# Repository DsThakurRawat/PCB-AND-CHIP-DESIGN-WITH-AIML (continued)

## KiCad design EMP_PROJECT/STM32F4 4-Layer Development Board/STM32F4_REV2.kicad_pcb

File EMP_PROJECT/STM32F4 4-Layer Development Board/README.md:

# STM32F4 4-Layer Development Board

**Project**: STM32F405RGT6 4-Layer Reference Development Board  
**Course / Subject**: Electronics Manufacturing & PCB Design (EMP)  
**Submission Date**: November 8, 2026  

---

## 👥 Team Details
* **Divyansh Rawat** (Lead Hardware & Validation Engineer) — **Roll No: 124EC0030**
* Rehan Afroz — **Roll No: 124EC0033**
* Ishan Pandey — **Roll No: 124EC0032**
* Dasari E S T Vishnu Vardhan — **Roll No: 124EC0010**

---

## 📜 Attribution & Provenance
This hardware design is adapted and re-routed from the open-source **STM32F4 Reference Design** by **Philip Salmony (Phil's Lab)**.  
In compliance with the **MIT License**, the original copyright and license terms are preserved in full in the accompanying [`LICENSE`](file:///home/divyansh-rawat/AIPCBDESIGN/EMP_PROJECT/STM32F4%204-Layer%20Development%20Board/LICENSE) file. The layout has been adapted for KiCad 9, with custom design rules, optimized copper plane definitions, and re-generated turnkey manufacturing deliverables.

---

## 🚀 Key Specifications
* **Microcontroller**: STMicroelectronics STM32F405RGT6 (Arm Cortex-M4, 168 MHz, 1MB Flash, 192KB SRAM, LQFP-64)
* **Stackup**: 4 Layers (F.Cu Signal - In1.Cu Solid GND - In2.Cu Solid +3.3V - B.Cu Signal/GND)
* **Power Supply**: Dual-input (7V–24V DC Screw Terminal & 5V USB-C) stepping down to +3.3V via MPS MP2359 1.4 MHz buck converter
* **USB Interface**: USB 2.0 Full-Speed Type-C with ST USBLC6-2SC6 low-capacitance ESD protection
* **Oscillator**: 16.000 MHz fundamental-mode crystal conforming to ST AN2867 gain margin standards
* **Debug**: Standardized 4-pin SWD programming header

---

## 📁 Package Manifest
- [`STM32F4_REV2.kicad_sch`](file:///home/divyansh-rawat/AIPCBDESIGN/EMP_PROJECT/STM32F4%204-Layer%20Development%20Board/STM32F4_REV2.kicad_sch) — Native KiCad 9 Schematic (0 ERC violations)
- [`STM32F4_REV2.kicad_pcb`](file:///home/divyansh-rawat/AIPCBDESIGN/EMP_PROJECT/STM32F4%204-Layer%20Development%20Board/STM32F4_REV2.kicad_pcb) — Native KiCad 9 Layout (0 DRC violations, 0 unconnected items)
- [`STM32F4_REV2.kicad_pro`](file:///home/divyansh-rawat/AIPCBDESIGN/EMP_PROJECT/STM32F4%204-Layer%20Development%20Board/STM32F4_REV2.kicad_pro) — KiCad 9 Project settings & design rules
- [`STM32F4_REV2.kicad_sym`](file:///home/divyansh-rawat/AIPCBDESIGN/EMP_PROJECT/STM32F4%204-Layer%20Development%20Board/STM32F4_REV2.kicad_sym) — Project symbol library cache
- [`manufacturing/`](file:///home/divyansh-rawat/AIPCBDESIGN/EMP_PROJECT/STM32F4%204-Layer%20Development%20Board/manufacturing/)
  - `STM32F4_REV2_gerbers.zip` — Production-ready Gerber & Excellon drill archive
  - `STM32F4_REV2_bom.csv` — Reconciled manufacturing Bill of Materials
  - `STM32F4_REV2_pos.csv` — Pick-and-place centroid positions
  - `STM32F4_REV2_schematic.pdf` & `STM32F4_REV2.pdf` — Vector schematic and layout plots
  - `ibom.html` — Interactive visual assembly BOM
  - `STM32F4_REV2_3d.png` — 3D raytraced rendering of current board
- [`DESIGN_CONSIDERATIONS.md`](file:///home/divyansh-rawat/AIPCBDESIGN/EMP_PROJECT/STM32F4%204-Layer%20Development%20Board/DESIGN_CONSIDERATIONS.md) — Comprehensive engineering caveats, calculations, and bring-up checklist
- [`PRESENTATION.md`](file:///home/divyansh-rawat/AIPCBDESIGN/EMP_PROJECT/STM32F4%204-Layer%20Development%20Board/PRESENTATION.md) — Slide deck presentation and review document
- [`verification/`](file:///home/divyansh-rawat/AIPCBDESIGN/EMP_PROJECT/STM32F4%204-Layer%20Development%20Board/verification/)
  - `erc-rerun.json` & `erc-rerun.rpt` (0 errors, 0 warnings)
  - `drc-rerun.json` & `drc-rerun.rpt` (0 violations, 0 unconnected, 0 parity issues)
  - `gerbers-check/` (freshly plotted verification Gerbers)

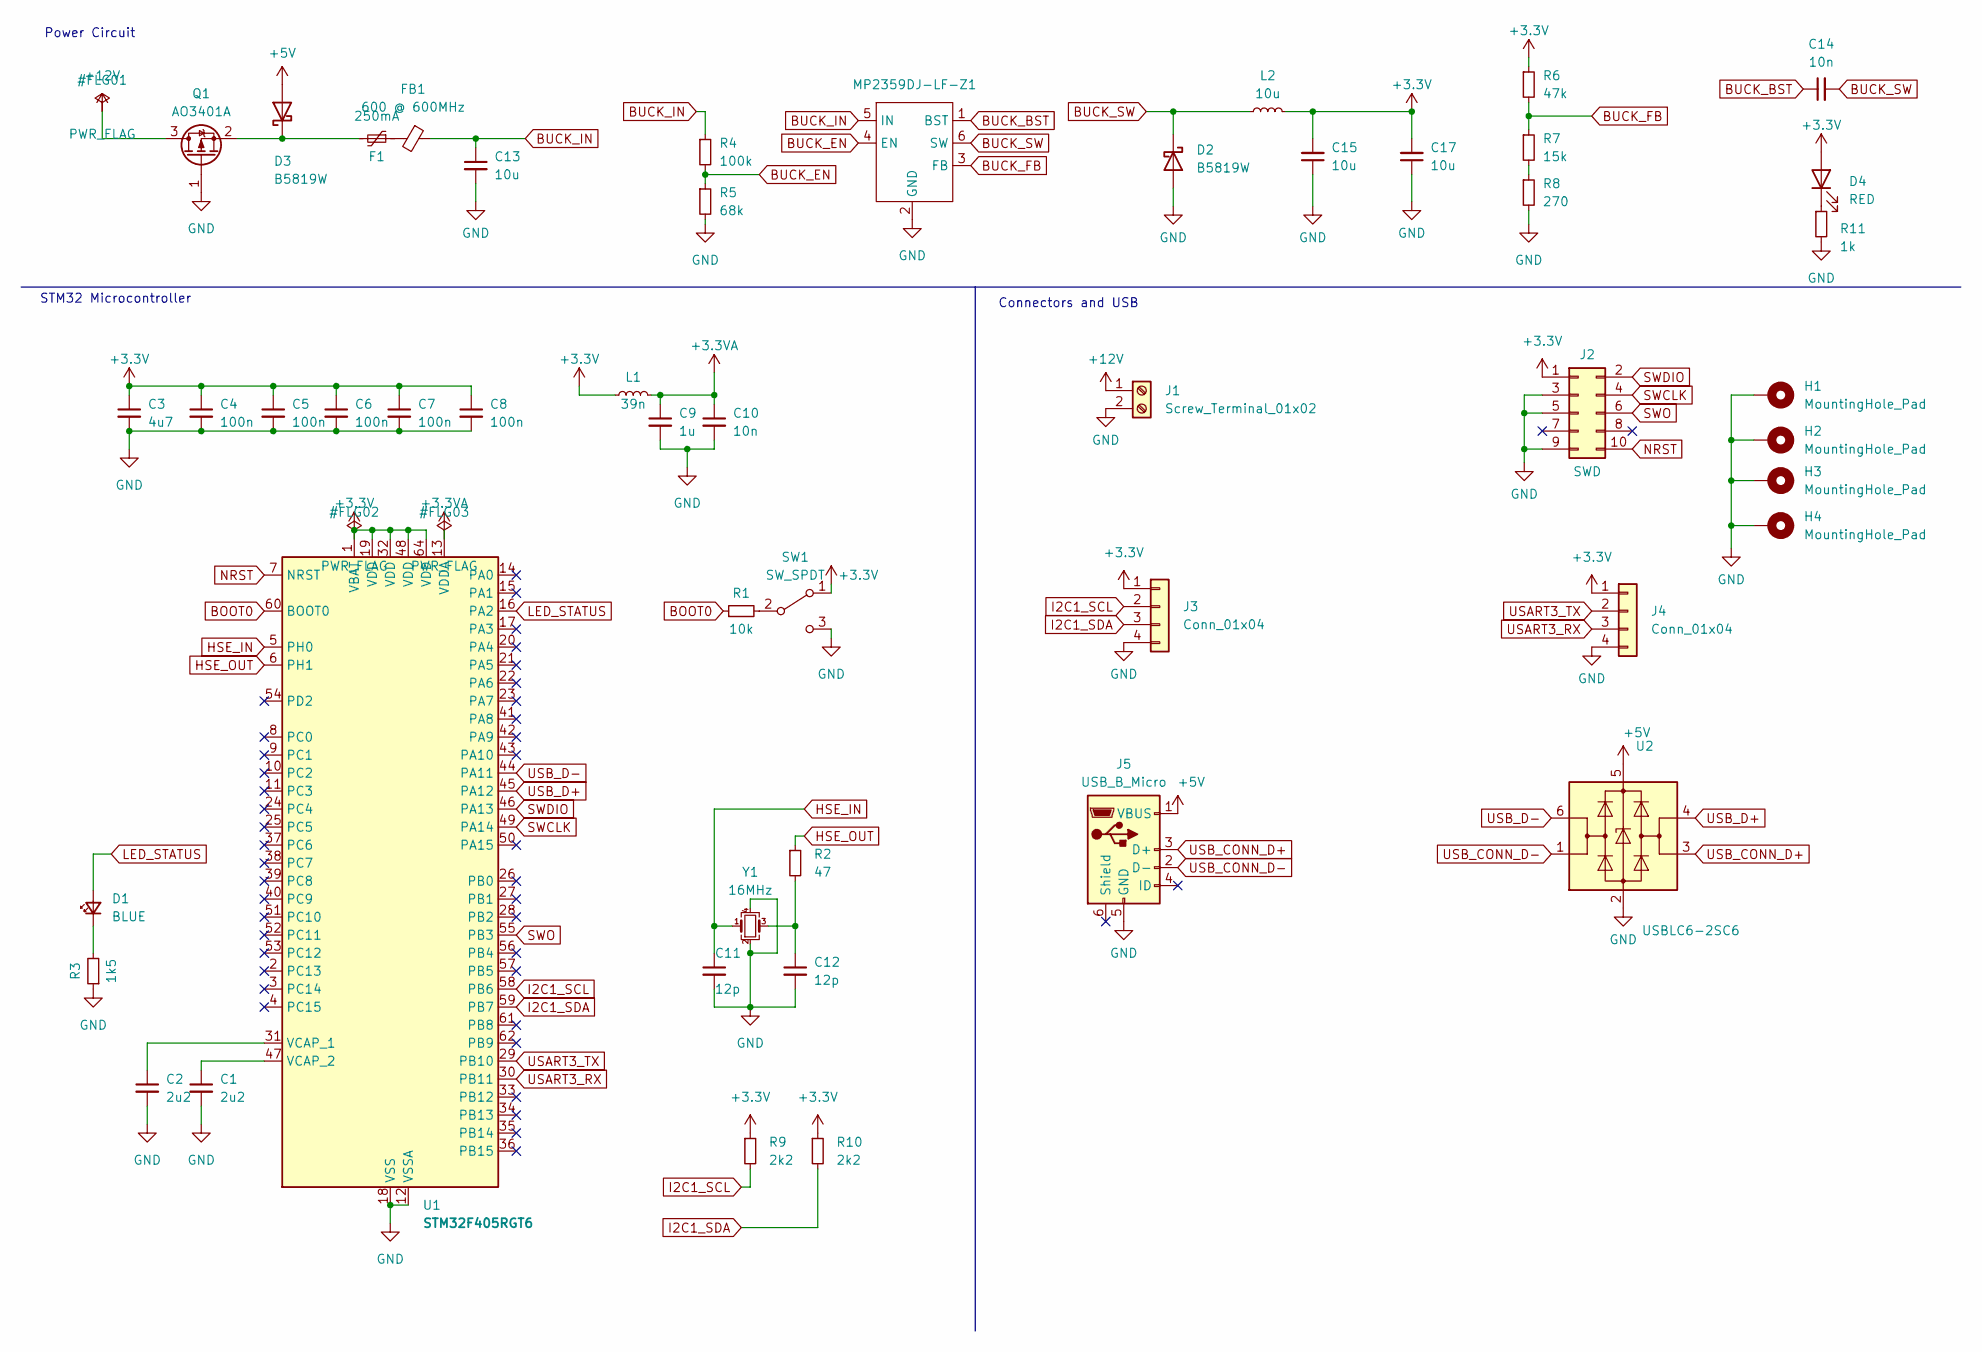
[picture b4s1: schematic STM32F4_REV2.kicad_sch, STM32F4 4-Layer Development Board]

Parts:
C1, C2: 2u2; C_0603_1608Metric
C3: 4u7; C_0603_1608Metric
C4, C5, C6, C7, C8: 100n; C_0402_1005Metric
C9: 1u; C_0402_1005Metric
C10: 10n; C_0402_1005Metric
C11, C12: 12p; C_0402_1005Metric
C13, C15, C17: 10u; C_1206_3216Metric
C14: 10n; C_0603_1608Metric
D1: BLUE; LED_0603_1608Metric
D2, D3: B5819W; D_SOD-123
D4: RED; LED_0603_1608Metric
F1: 250mA; Fuse_1206_3216Metric
FB1: 600 @ 600MHz; L_0805_2012Metric
H1, H2, H3, H4: MountingHole_Pad; MountingHole_4.3mm_M4_Pad_Via
J1: Screw_Terminal_01x02; TerminalBlock_Phoenix_PT-1,5-2-3.5-H_1x02_P3.50mm_Horizontal
J2: SWD; PinHeader_2x05_P1.27mm_Vertical_SMD
J3, J4: Conn_01x04; Molex_PicoBlade_53048-0410_1x04_P1.25mm_Horizontal
J5: USB_B_Micro; USB_Micro-B_GCT_USB3076-30-A
L1: 39n; L_0402_1005Metric
L2: 10u; L_TracoPower_TCK-047_5.2x5.8mm
MP2359DJ-LF-Z1: SOT-23-6
Q1: AO3401A; SOT-23
R1: 10k; R_0402_1005Metric
R2: 47; R_0402_1005Metric
R3: 1k5; R_0603_1608Metric
R4: 100k; R_0603_1608Metric
R5: 68k; R_0603_1608Metric
R6: 47k; R_0603_1608Metric
R7: 15k; R_0603_1608Metric
R8: 270; R_0603_1608Metric
R9, R10: 2k2; R_0402_1005Metric
R11: 1k; R_0603_1608Metric
SW1: SW_SPDT; SW_SPDT_PCM12
U1: STM32F405RGT6; LQFP-64_10x10mm_P0.5mm
U2: USBLC6-2SC6; SOT-23-6
Y1: 16MHz; Crystal_SMD_3225-4Pin_3.2x2.5mm

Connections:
+3.3V: C3.1, C4.1, C5.1, C6.1, C7.1, C8.1, C15.2, C17.2, D4.2 (A), J2.1, J3.1, J4.1, L1.1, L2.2, R6.1, R9.1, R10.1, SW1.1 (A), U1.1 (VBAT), U1.19 (VDD), U1.32 (VDD), U1.48 (VDD), U1.64 (VDD)
+3.3VA: C9.1, C10.1, L1.2, U1.13 (VDDA)
+5V: D3.2 (A), J5.1 (VBUS), U2.5 (VBUS)
+12V: J1.1, Q1.3 (D)
BOOT0: R1.1, U1.60 (BOOT0)
BUCK_BST: C14.1, MP2359DJ-LF-Z1.1 (BST)
BUCK_EN: MP2359DJ-LF-Z1.4 (EN), R4.2, R5.1
BUCK_FB: MP2359DJ-LF-Z1.3 (FB), R6.2, R7.1
BUCK_IN: C13.1, FB1.1, MP2359DJ-LF-Z1.5 (IN), R4.1
BUCK_SW: C14.2, D2.1 (K), L2.1, MP2359DJ-LF-Z1.6 (SW)
GND: C1.2, C2.2, C3.2, C4.2, C5.2, C6.2, C7.2, C8.2, C9.2, C10.2, C11.2, C12.2, C13.2, C15.1, C17.1, D2.2 (A), H1.1, H2.1, H3.1, H4.1, J1.2, J2.3, J2.5, J2.9, J3.4, J4.4, J5.5 (GND), MP2359DJ-LF-Z1.2 (GND), Q1.1 (G), R3.1, R5.2, R8.2, R11.2, SW1.3 (C), U1.12 (VSSA), U1.18 (VSS), U1.63 (VSS), U2.2 (GND), Y1.2, Y1.4
HSE_IN: C11.1, U1.5 (PH0), Y1.1
HSE_OUT: R2.1, U1.6 (PH1)
I2C1_SCL: J3.2, R9.2, U1.58 (PB6)
I2C1_SDA: J3.3, R10.2, U1.59 (PB7)
LED_STATUS: D1.2 (A), U1.16 (PA2)
NRST: J2.10, U1.7 (NRST)
unnamed: C12.1, R2.2, Y1.3
unnamed: D1.1 (K), R3.2
unnamed: D3.1 (K), F1.2, Q1.2 (S)
unnamed: D4.1 (K), R11.1
unnamed: F1.1, FB1.2
unnamed: R7.2, R8.1
unnamed: R1.2, SW1.2 (B)
unnamed: C2.1, U1.31 (VCAP_1)
unnamed: C1.1, U1.47 (VCAP_2)
SWCLK: J2.4, U1.49 (PA14)
SWDIO: J2.2, U1.46 (PA13)
SWO: J2.6, U1.55 (PB3)
USART3_RX: J4.3, U1.30 (PB11)
USART3_TX: J4.2, U1.29 (PB10)
USB_CONN_D+: J5.3 (D+), U2.3 (I/O2)
USB_CONN_D-: J5.2 (D-), U2.1 (I/O1)
USB_D+: U1.45 (PA12), U2.4 (I/O2)
USB_D-: U1.44 (PA11), U2.6 (I/O1)

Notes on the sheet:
Power Circuit
STM32 Microcontroller
Connectors and USB

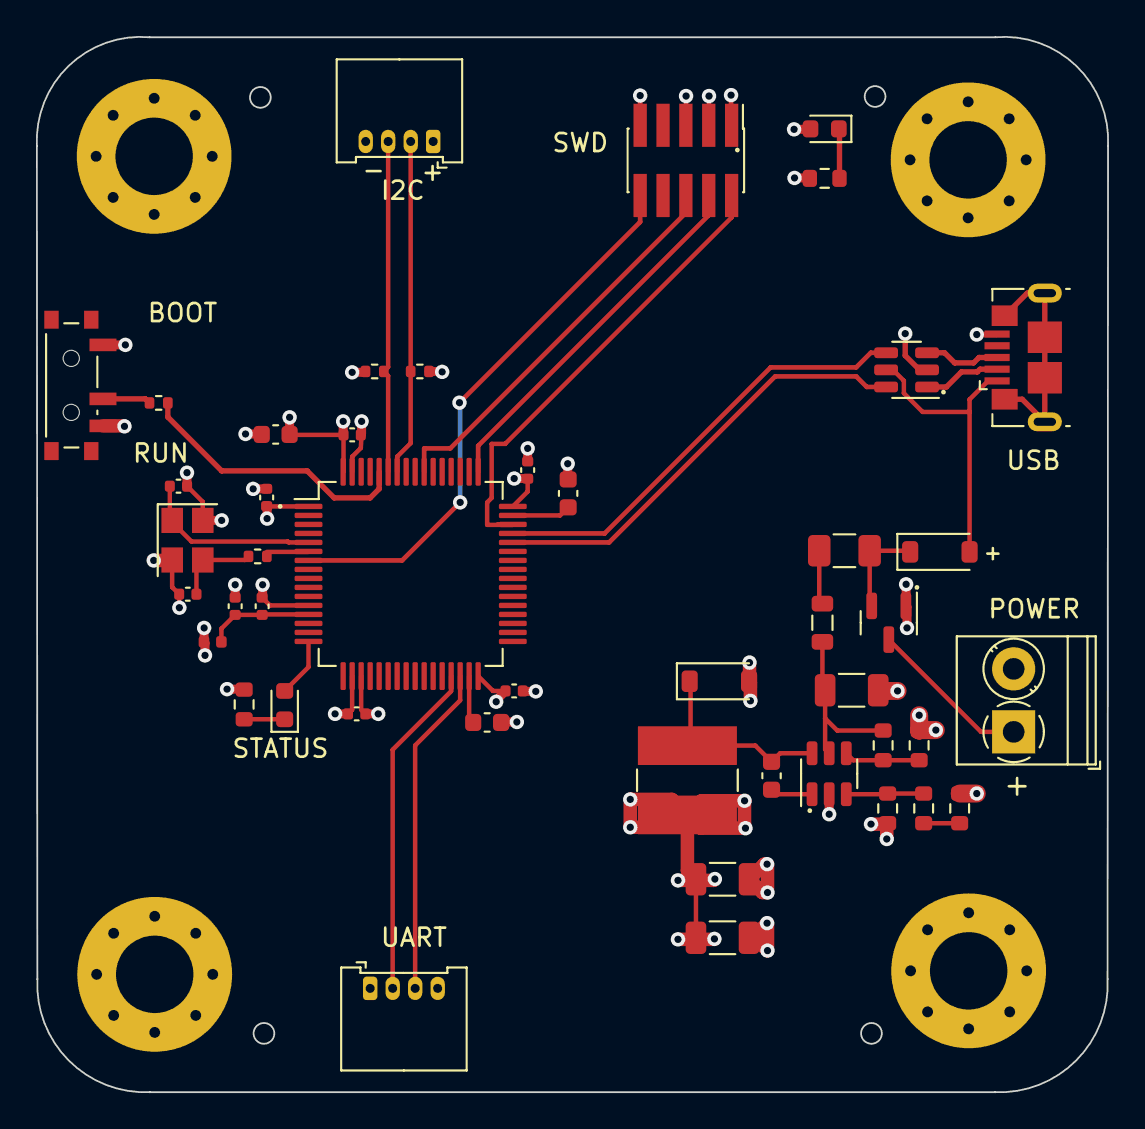
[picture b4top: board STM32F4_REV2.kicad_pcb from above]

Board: 4 copper layers, 59.5 x 58.6 mm, 50 parts (0 on the bottom side), 35 nets.

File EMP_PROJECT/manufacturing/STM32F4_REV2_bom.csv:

"Refs","Value","Footprint","Qty","DNP"
"C1","2u2","Capacitor_SMD:C_0603_1608Metric","1",""
"C2","2u2","Capacitor_SMD:C_0603_1608Metric","1",""
"C3","4u7","Capacitor_SMD:C_0603_1608Metric","1",""
"C4","100n","Capacitor_SMD:C_0402_1005Metric","1",""
"C5","100n","Capacitor_SMD:C_0402_1005Metric","1",""
"C6","100n","Capacitor_SMD:C_0402_1005Metric","1",""
"C7","100n","Capacitor_SMD:C_0402_1005Metric","1",""
"C8","100n","Capacitor_SMD:C_0402_1005Metric","1",""
"C9","1u","Capacitor_SMD:C_0402_1005Metric","1",""
"C10","10n","Capacitor_SMD:C_0402_1005Metric","1",""
"C11","12p","Capacitor_SMD:C_0402_1005Metric","1",""
"C12","12p","Capacitor_SMD:C_0402_1005Metric","1",""
"C13","10u","Capacitor_SMD:C_1206_3216Metric","1",""
"C14","10n","Capacitor_SMD:C_0603_1608Metric","1",""
"C15","10u","Capacitor_SMD:C_1206_3216Metric","1",""
"C17","10u","Capacitor_SMD:C_1206_3216Metric","1",""
"D1","BLUE","LED_SMD:LED_0603_1608Metric","1",""
"D2","B5819W","Diode_SMD:D_SOD-123","1",""
"D3","B5819W","Diode_SMD:D_SOD-123","1",""
"D4","RED","LED_SMD:LED_0603_1608Metric","1",""
"F1","250mA","Fuse:Fuse_1206_3216Metric","1",""
"FB1","600 @ 600MHz","Inductor_SMD:L_0805_2012Metric","1",""
"H1","MountingHole_Pad","MountingHole:MountingHole_4.3mm_M4_Pad_Via","1",""
"H2","MountingHole_Pad","MountingHole:MountingHole_4.3mm_M4_Pad_Via","1",""
"H3","MountingHole_Pad","MountingHole:MountingHole_4.3mm_M4_Pad_Via","1",""
"H4","MountingHole_Pad","MountingHole:MountingHole_4.3mm_M4_Pad_Via","1",""
"J1","Screw_Terminal_01x02","TerminalBlock_Phoenix:TerminalBlock_Phoenix_PT-1,5-2-3.5-H_1x02_P3.50mm_Horizontal","1",""
"J2","SWD","Connector_PinHeader_1.27mm:PinHeader_2x05_P1.27mm_Vertical_SMD","1",""
"J3","Conn_01x04","Connector_Molex:Molex_PicoBlade_53048-0410_1x04_P1.25mm_Horizontal","1",""
"J4","Conn_01x04","Connector_Molex:Molex_PicoBlade_53048-0410_1x04_P1.25mm_Horizontal","1",""
"J5","USB_B_Micro","Connector_USB:USB_Micro-B_GCT_USB3076-30-A","1",""
"L1","39n","Inductor_SMD:L_0402_1005Metric","1",""
"L2","10u","Inductor_SMD:L_TracoPower_TCK-047_5.2x5.8mm","1",""
"MP2359DJ-LF-Z1","~","Package_TO_SOT_SMD:SOT-23-6","1",""
"Q1","AO3401A","Package_TO_SOT_SMD:SOT-23","1",""
"R1","10k","Resistor_SMD:R_0402_1005Metric","1",""
"R2","47","Resistor_SMD:R_0402_1005Metric","1",""
"R3","1k5","Resistor_SMD:R_0603_1608Metric","1",""
"R4","100k","Resistor_SMD:R_0603_1608Metric","1",""
"R5","68k","Resistor_SMD:R_0603_1608Metric","1",""
"R6","47k","Resistor_SMD:R_0603_1608Metric","1",""
"R7","15k","Resistor_SMD:R_0603_1608Metric","1",""
"R8","270","Resistor_SMD:R_0603_1608Metric","1",""
"R9","2k2","Resistor_SMD:R_0402_1005Metric","1",""
"R10","2k2","Resistor_SMD:R_0402_1005Metric","1",""
"R11","1k","Resistor_SMD:R_0603_1608Metric","1",""
"SW1","SW_SPDT","Button_Switch_SMD:SW_SPDT_PCM12","1",""
"U1","STM32F405RGT6","Package_QFP:LQFP-64_10x10mm_P0.5mm","1",""
"U2","USBLC6-2SC6","Package_TO_SOT_SMD:SOT-23-6","1",""
"Y1","16MHz","Crystal:Crystal_SMD_3225-4Pin_3.2x2.5mm","1",""

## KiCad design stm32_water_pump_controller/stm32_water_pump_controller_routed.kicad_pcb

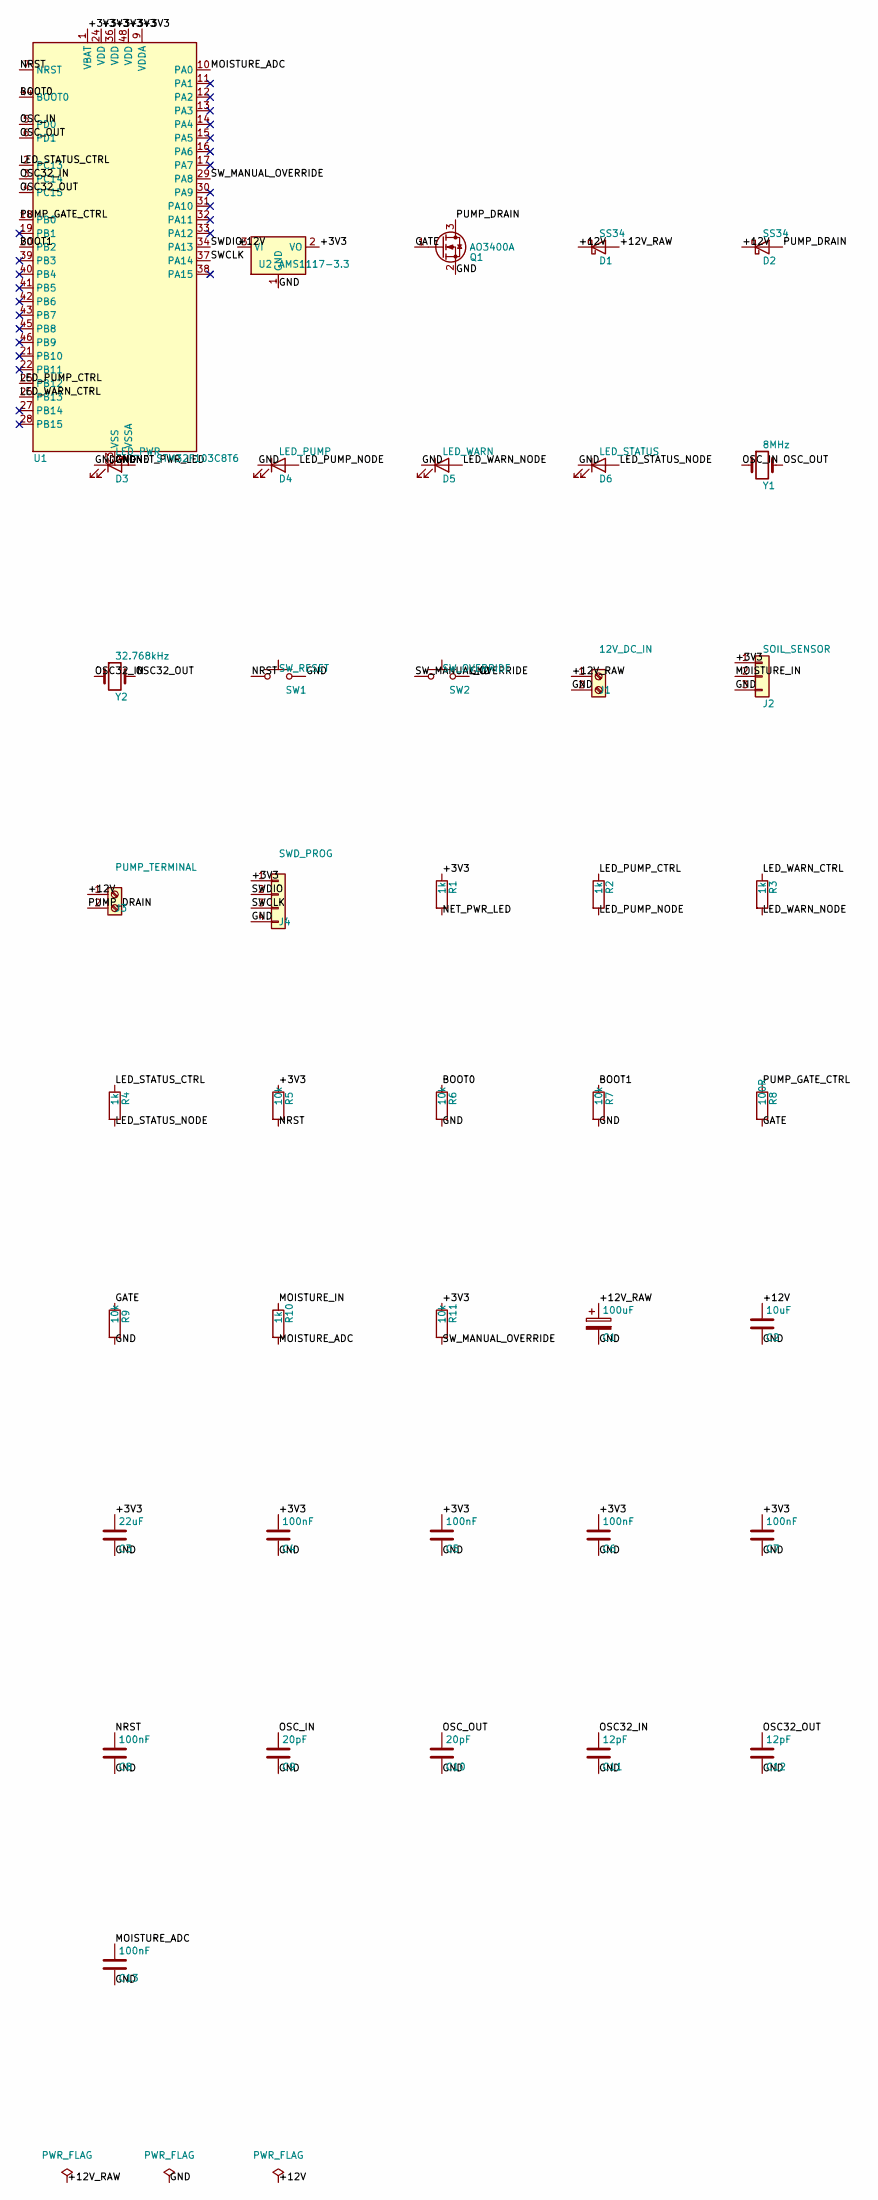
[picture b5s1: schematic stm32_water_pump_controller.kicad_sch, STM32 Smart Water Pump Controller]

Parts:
C1: 100uF; CP_Radial_D6.3mm_P2.50mm
C2: 10uF; C_0805_2012Metric
C3: 22uF; C_0805_2012Metric
C4, C5, C6, C7, C8, C13: 100nF; C_0805_2012Metric
C9, C10: 20pF; C_0805_2012Metric
C11, C12: 12pF; C_0805_2012Metric
D1, D2: SS34; D_SMA
D3: LED_PWR; LED_0805_2012Metric
D4: LED_PUMP; LED_0805_2012Metric
D5: LED_WARN; LED_0805_2012Metric
D6: LED_STATUS; LED_0805_2012Metric
J1: 12V_DC_IN; TerminalBlock_Phoenix_MKDS-1,5-2-5.08_1x02_P5.08mm_Horizont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
J2: SOIL_SENSOR; PinHeader_1x03_P2.54mm_Vertical
J3: PUMP_TERMINAL; TerminalBlock_Phoenix_MKDS-1,5-2-5.08_1x02_P5.08mm_Horizont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
J4: SWD_PROG; PinHeader_1x04_P2.54mm_Vertical
Q1: AO3400A; SOT-23
R1, R2, R3, R4, R10: 1k; R_0805_2012Metric
R5, R6, R7, R9, R11: 10k; R_0805_2012Metric
R8: 100R; R_0805_2012Metric
SW1: SW_RESET; SW_PUSH_6mm
SW2: SW_OVERRIDE; SW_PUSH_6mm
U1: STM32F103C8T6; LQFP-48_7x7mm_P0.5mm
U2: AMS1117-3.3; SOT-223-3_TabPin2
Y1: 8MHz; Crystal_SMD_5032-2Pin_5.0x3.2mm
Y2: 32.768kHz; Crystal_SMD_3215-2Pin_3.2x1.5mm

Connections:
+3V3: C3.1, C4.1, C5.1, C6.1, C7.1, J2.1, J4.1, R1.1, R5.1, R11.1, U1.1 (VBAT), U1.9 (VDDA), U1.24 (VDD), U1.36 (VDD), U1.48 (VDD), U2.2 (VO)
+12V: C2.1, D1.1 (K), D2.1 (K), J3.1, U2.3 (VI)
+12V_RAW: C1.1, D1.2 (A), J1.1
BOOT0: R6.1, U1.44 (BOOT0)
BOOT1: R7.1, U1.20 (PB2)
GATE: Q1.1 (G), R8.2, R9.1
GND: C1.2, C2.2, C3.2, C4.2, C5.2, C6.2, C7.2, C8.2, C9.2, C10.2, C11.2, C12.2, C13.2, D3.1 (K), D4.1 (K), D5.1 (K), D6.1 (K), J1.2, J2.3, J4.4, Q1.2 (S), R6.2, R7.2, R9.2, SW1.2, SW2.2, U1.8 (VSSA), U1.23 (VSS), U1.35 (VSS), U1.47 (VSS), U2.1 (GND)
LED_PUMP_CTRL: R2.1, U1.25 (PB12)
LED_PUMP_NODE: D4.2 (A), R2.2
LED_STATUS_CTRL: R4.1, U1.2 (PC13)
LED_STATUS_NODE: D6.2 (A), R4.2
LED_WARN_CTRL: R3.1, U1.26 (PB13)
LED_WARN_NODE: D5.2 (A), R3.2
MOISTURE_ADC: C13.1, R10.2, U1.10 (PA0)
MOISTURE_IN: J2.2, R10.1
NET_PWR_LED: D3.2 (A), R1.2
NRST: C8.1, R5.2, SW1.1, U1.7 (NRST)
OSC32_IN: C11.1, U1.3 (PC14), Y2.1
OSC32_OUT: C12.1, U1.4 (PC15), Y2.2
OSC_IN: C9.1, U1.5 (PD0), Y1.1
OSC_OUT: C10.1, U1.6 (PD1), Y1.2
PUMP_DRAIN: D2.2 (A), J3.2, Q1.3 (D)
PUMP_GATE_CTRL: R8.1, U1.18 (PB0)
SWCLK: J4.3, U1.37 (PA14)
SWDIO: J4.2, U1.34 (PA13)
SW_MANUAL_OVERRIDE: R11.2, SW2.1, U1.29 (PA8)

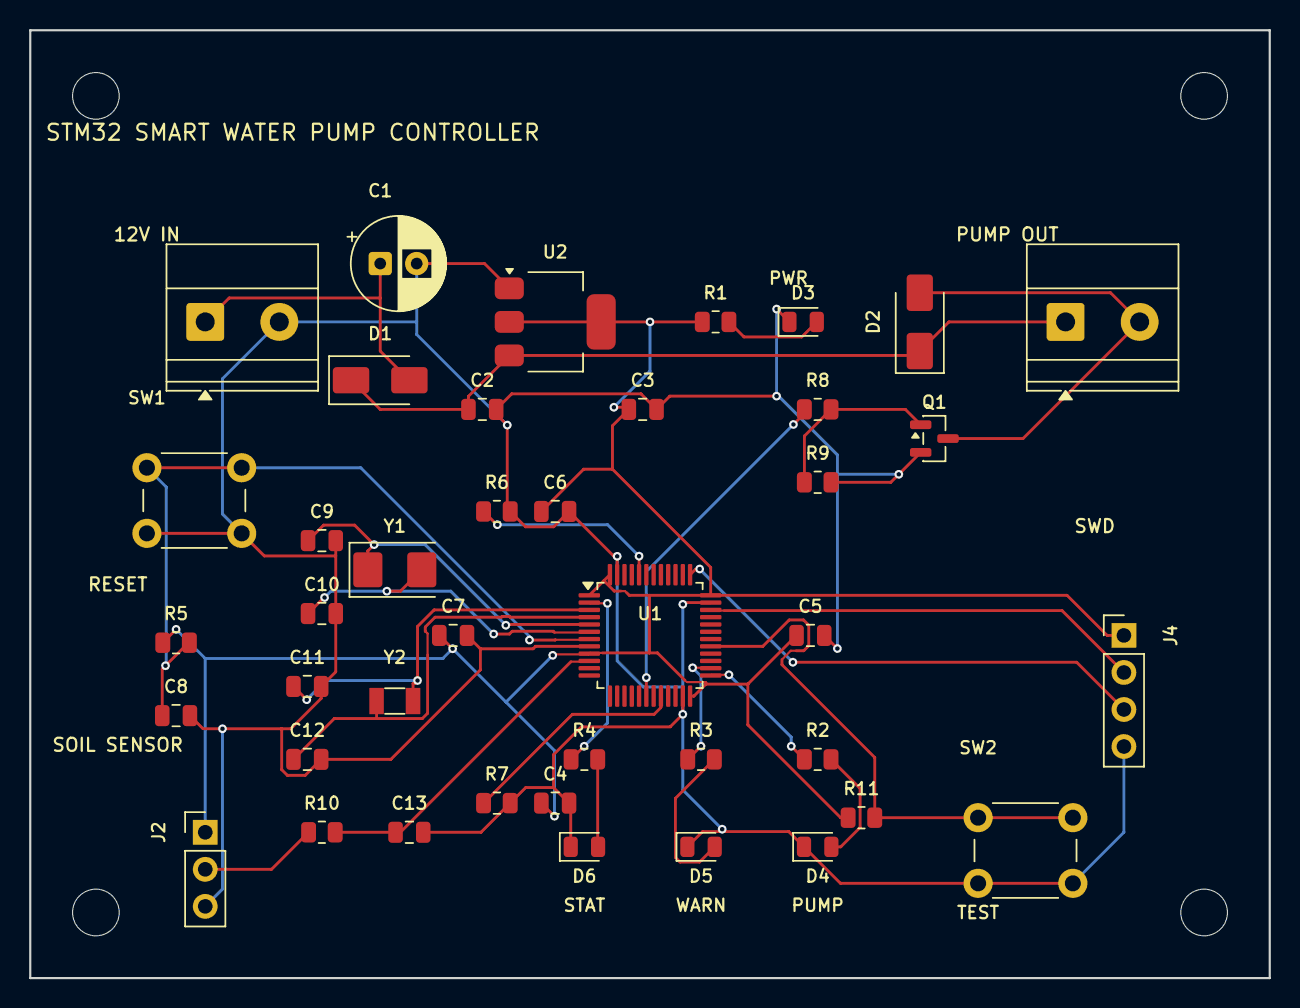
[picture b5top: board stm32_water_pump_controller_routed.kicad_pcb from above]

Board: 2 copper layers, 85.0 x 65.0 mm, 45 parts (0 on the bottom side), 26 nets.

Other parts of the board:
H1, H2, H3, H4: MountingHole_3.2mm_M3

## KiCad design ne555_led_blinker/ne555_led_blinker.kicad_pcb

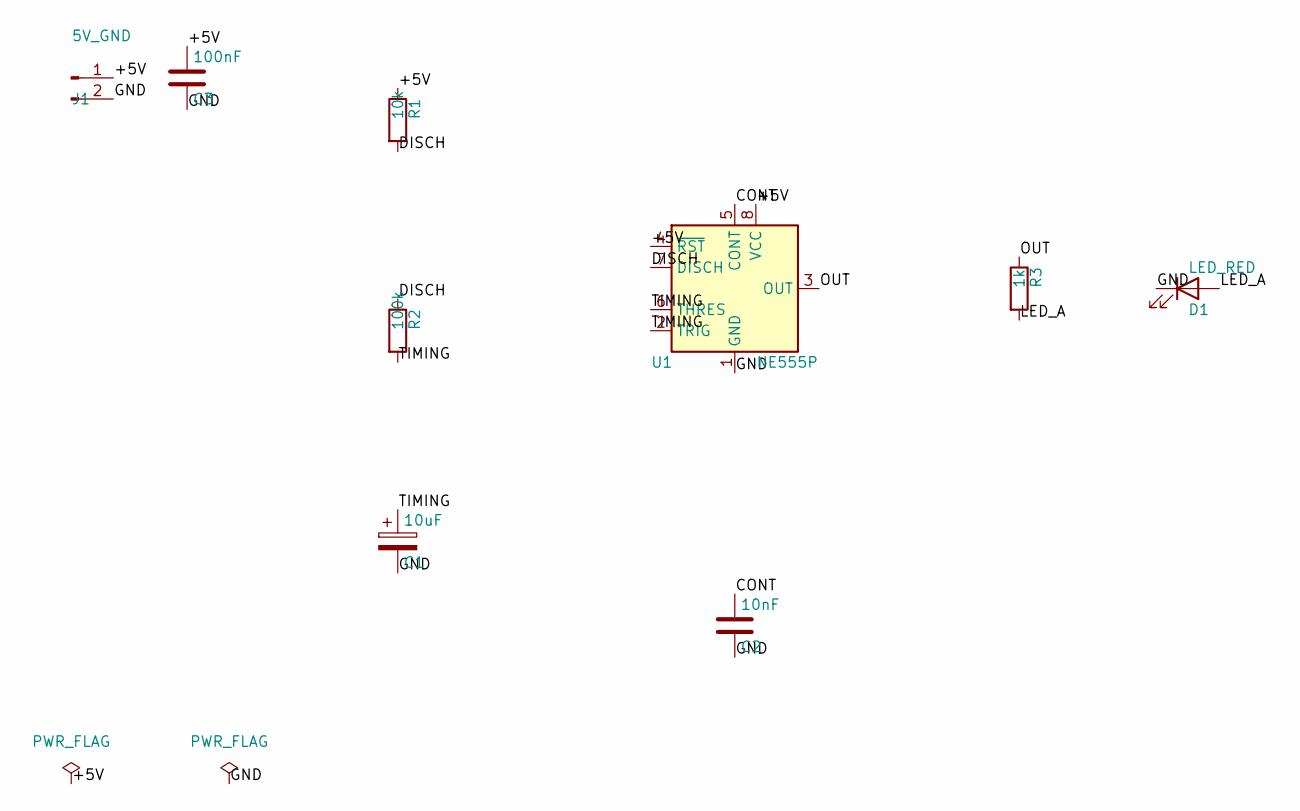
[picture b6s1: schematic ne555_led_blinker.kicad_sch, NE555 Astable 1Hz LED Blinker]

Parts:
C1: 10uF; CP_Radial_D5.0mm_P2.50mm
C2: 10nF; C_Disc_D5.0mm_W2.5mm_P5.00mm
C3: 100nF; C_Disc_D5.0mm_W2.5mm_P5.00mm
D1: LED_RED; LED_D5.0mm
J1: 5V_GND; PinHeader_1x02_P2.54mm_Vertical
R1: 10k; R_Axial_DIN0207_L6.3mm_D2.5mm_P7.62mm_Horizontal
R2: 100k; R_Axial_DIN0207_L6.3mm_D2.5mm_P7.62mm_Horizontal
R3: 1k; R_Axial_DIN0207_L6.3mm_D2.5mm_P7.62mm_Horizontal
U1: NE555P; DIP-8_W7.62mm

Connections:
+5V: C3.1, J1.1, R1.1, U1.4 (~RST), U1.8 (VCC)
CONT: C2.1, U1.5 (CONT)
DISCH: R1.2, R2.1, U1.7 (DISCH)
GND: C1.2, C2.2, C3.2, D1.1 (K), J1.2, U1.1 (GND)
LED_A: D1.2 (A), R3.2
OUT: R3.1, U1.3 (OUT)
TIMING: C1.1, R2.2, U1.2 (TRIG), U1.6 (THRES)

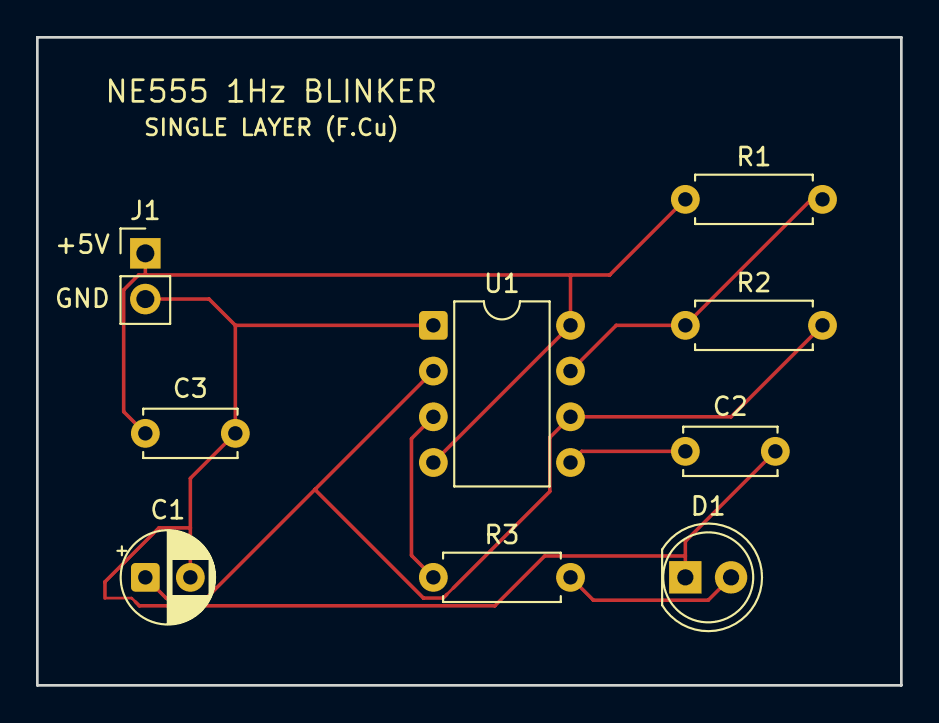
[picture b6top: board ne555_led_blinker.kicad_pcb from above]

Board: 2 copper layers, 48.0 x 36.0 mm, 9 parts (0 on the bottom side), 7 nets.

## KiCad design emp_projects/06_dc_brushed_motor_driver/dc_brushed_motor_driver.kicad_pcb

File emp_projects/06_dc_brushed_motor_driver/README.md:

# High-Power DC Brushed Motor Driver PCB

## 📌 Project Overview
**Course Experiment:** Electronic Measurement Practices (EMP)  
**PCB Architecture:** 2-Layer Controlled Design  
**Primary Controller:** Embedded Controller  
**Deliverables Status:** Complete Manufacturing Package Verified (Gerbers, Drill, Pos CSV, iBOM, 3D Render)

---

## 🎯 Description & Operational Principles
High-power discrete MOSFET H-Bridge driver with dedicated bootstrap gate drivers, optoisolated PWM and direction inputs, current sensing shunt, and heavy 2oz copper output traces.

### Key Features & Subsystems
- **Processor & Logic Core:** High-efficiency architecture designed for reliable embedded operation.
- **Power Management & Regulation:** Low-noise power rail distribution with dedicated filtering and bulk decouple stages.
- **Sensory & Peripheral Interfacing:** Industrial standard interconnect headers with ESD and reverse polarity protection.
- **Fabrication & Assembly Optimization:** Standard 0805 SMD passives and leaded THT power devices for high manufacturing yield and inspectability.

---

## 🛠️ Bill of Materials (BOM Summary)

| Reference | Component Value | Package / Footprint | Description |
|:---:|:---:|:---:|:---|

---

## 🏭 Manufacturing Deliverables & Artifacts

All production files have been generated in `manufacturing/`:
- **Gerber Layers (RS-274X):** Copper, solder masks, silkscreen, and board edge cuts (`manufacturing/gerbers/`)
- **Excellon Drill Files:** Plated and non-plated drill hole coordinates (`manufacturing/gerbers/*.drl`)
- **Fabricator ZIP Archive:** Single upload archive for PCB fabrication houses (`manufacturing/dc_brushed_motor_driver_gerbers.zip`)
- **Pick-and-Place Position CSV:** Centroid data for automated SMT placement machines (`manufacturing/dc_brushed_motor_driver_pos.csv`)
- **Interactive HTML BOM:** High-efficiency browser inspection and interactive assembly tool (`manufacturing/ibom.html`)
- **Altium-Style 3D Render:** Photorealistic perspective view with floor reflection shaders (`manufacturing/dc_brushed_motor_driver_3d.png`)

---

## 📐 Mechanical & Layout Constraints
- **Board Outline:** 80 mm × 60 mm
- **Layer Count:** 2 Layers (FR-4, 1.6mm thickness, 1oz/2oz copper)
- **Minimum Trace Width:** 0.20 mm (8 mil)
- **Minimum Clearance:** 0.20 mm (8 mil)
- **Via Drill / Diameter:** 0.40 mm drill / 0.80 mm annular ring pad

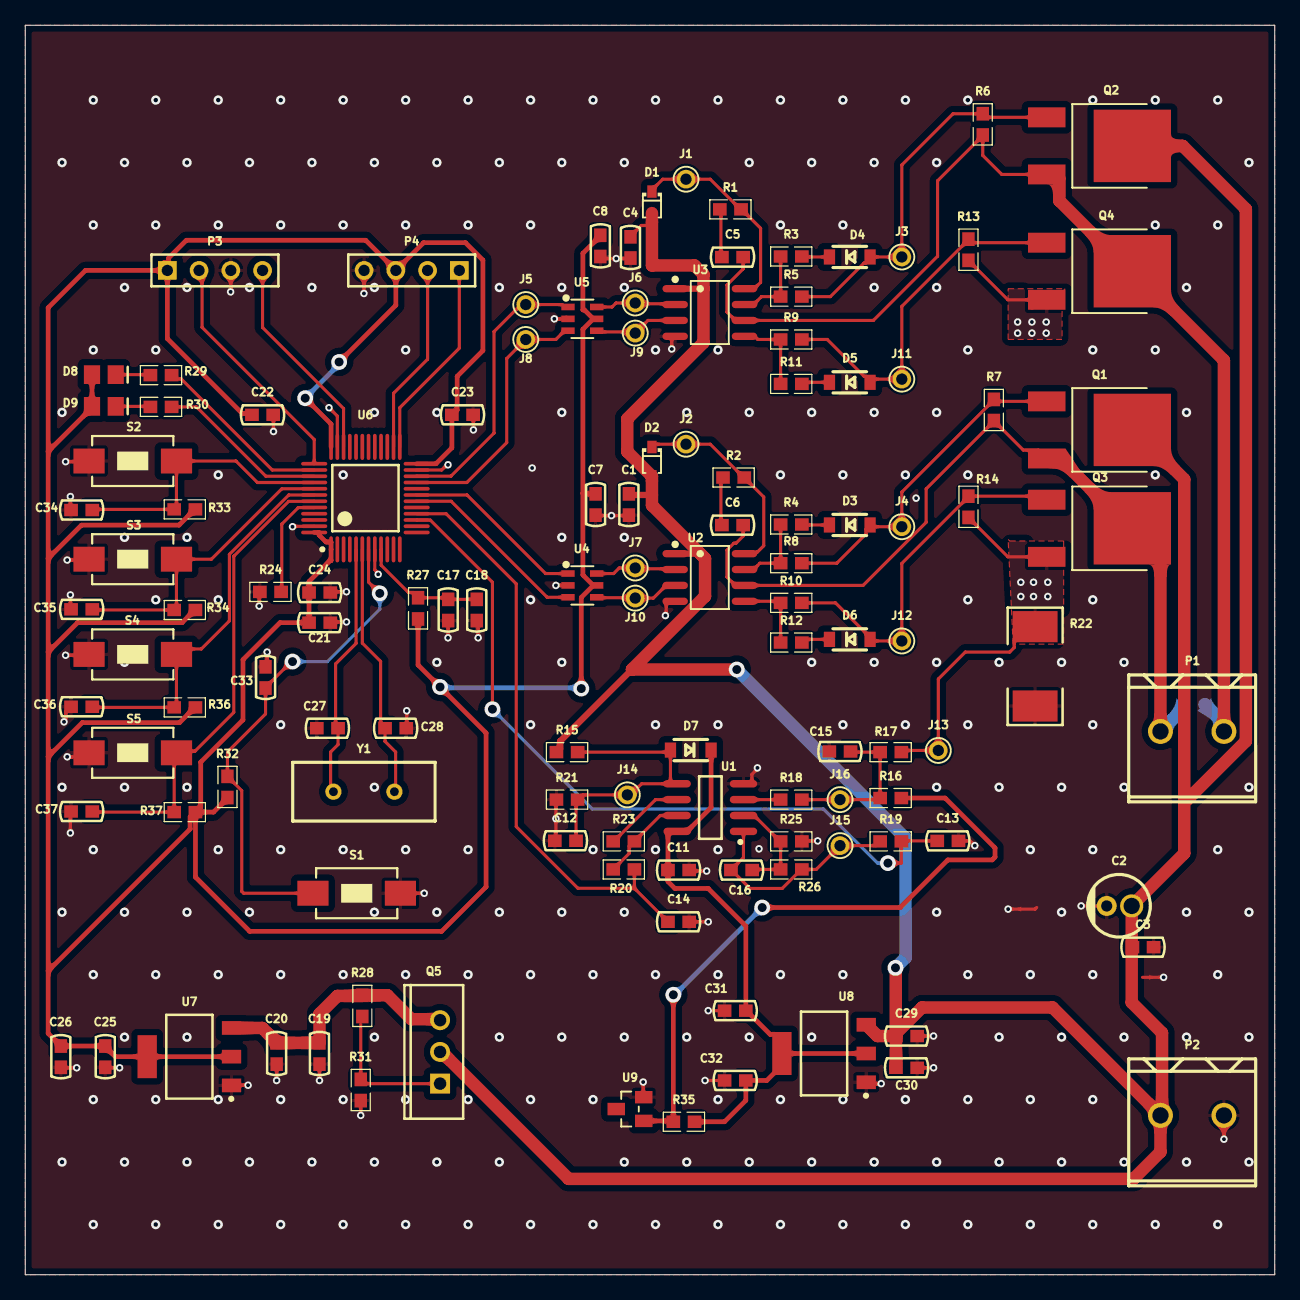
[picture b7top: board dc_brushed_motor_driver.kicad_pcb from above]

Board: 2 copper layers, 100.0 x 100.0 mm, 122 parts (1 on the bottom side), 60 nets.

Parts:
C1, C4, C19, C24, C25, C29, C31: 10uF; C-RAD-0603
C2: 100uF; CAP-TH_BD5.0-P2.00-D0.5-FD-A
C3, C5, C6, C7, C8, C9, C11, C12, C16, C20, C21, C22, C23, C26, C30, C32, C33, C34, C35, C36, C37: 100nF; C-RAD-0603
C13, C14: 1nF; C-RAD-0603
C15, C18: 1uF; C-RAD-0603
C17: 10nF; C-RAD-0603
C27, C28: 16pF; C-RAD-0603
D1, D2: 1N4007WS; SOD-323_L1.8-W1.3-LS2.5-RD
D3, D4, D5, D6: 1N5819W; SOD-123_L2.7-W1.6-LS3.7-R-RD
D7: 1N4007; SOD-123_L2.7-W1.6-LS3.7-R-RD
D8, D9: LED0; LED_0805
J1, J2, J3, J4, J5, J6, J7, J8, J9, J10, J11, J12, J13, J14, J15, J16: CHECK; CHECK-A
P1, P2: WJ500V-5.08-2P; CONN-TH_2P-P5.00_WJ500V-5.08-2P
P3, P4: Header 4; HDR4X1_A
Q1, Q2, Q3, Q4: NCE6020AK; TO-252-2_L6.6-W6.1-P4.57-LS10.1-TL-CW
Q5: MOSFET-P; TO-220AB
R1, R2, R3, R4, R5, R8, R9, R10, R11, R12, R19, R20, R27: 10; 0603-1
R6, R7, R13, R14: 100k; 0603-1
R15: 30k; 0603-1
R16, R26: 20K; 0603-1
R17, R18, R25, R28, R29, R30, R31: 1k; 0603-1
R21, R23, R24, R32, R33, R34, R35, R36, R37: 10k; 0603-1
R22: 10mR; 2512
S1, S2, S3, S4, S5: SW-PB; SW_PB2_A1
U1: LMV358; NSO8_N
U2, U3: XJNG2103; SOIC-8_L4.9-W3.9-P1.27-LS6.0-BL
U4, U5: SN74LVC2G17DBVR; SOT-23-6_L2.9-W1.6-P0.95-LS2.8-BL
U6: STM32F103C; LQFP-48_M
U7, U8: SPX1117M3-3.3; SOT-223
U9: LM385M3-1.2/TR; SOT-23-3_L2.9-W1.3-P1.90-LS2.4-BR
Y1: XTAL; HC-49UX-TH_L11.4-W4.7-P4.88

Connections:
12V: C1.1, C2.1, C3.2, C4.1, C29.2, C30.2, D1.2, D2.2, P2.2, Q1.2, Q2.2, Q5.D, R15.1, U2.1, U3.1, U8.3
A3.3V: C11.1, C31.2, C32.2, D7.2, R35.2, U1.8, U8.2, U8.4
ADC_CUR: C13.1, R19.1, U6.15
ADC_VOL: C14.1, R20.1, U6.16
CLK: P4.2, U6.26
GND: C1.2, C2.2, C3.1, C4.2, C7.2, C8.2, C11.2, C12.2, C13.2, C14.2, C15.1, C17.1, C18.1, C19.1, C20.1, C21.1, C22.1, C23.1, C24.1, C25.1, C26.1, C27.1, C28.1, C29.1, C30.1, C31.1, C32.1, C33.1, C34.1, C35.1, C36.1, C37.1, P2.1, P3.3, P4.4, R21.2, R22.1, R24.2, R25.2, R31.1, S1.1, S2.1, S3.1, S4.1, S5.1, U1.4, U2.4, U3.4, U4.2, U5.2, U6.8, U6.23, U6.35, U6.47, U7.1, U8.1, U9.2
LED1: R29.1, U6.38
LED2: R30.1, U6.39
NRST: C33.2, R32.1, S1.2, U6.7
NetC5_1: C5.1, C9.2, P1.1, Q2.3, Q4.2, R6.2, U3.6
NetC5_2: C5.2, R1.1
NetC6_1: C6.1, C9.1, P1.2, Q1.3, Q3.2, R7.2, U2.6
NetC6_2: C6.2, R2.2
NetC12_1: C12.1, D7.1, J14.1, R15.2, R21.1, U1.5
NetC15_2: C15.2, J16.1, R16.2, R17.1, R18.2
NetC16_1: C16.1, J15.1, R19.2, R26.1, U1.1
NetC16_2: C16.2, R25.1, R26.2, U1.2
NetC17_2: C17.2, C18.2, R27.1, U6.9
NetC19_2: C19.2, C20.2, Q5.S, R28.2, U7.3
NetD1_1: D1.1, J1.1, R1.2, U3.8
NetD2_1: D2.1, J2.1, R2.1, U2.8
NetD3_1: D3.1, J4.1, Q1.1, R7.1, R8.2
NetD3_2: D3.2, R4.2
NetD4_1: D4.1, J3.1, Q2.1, R5.2, R6.1
NetD4_2: D4.2, R3.2
NetD5_1: D5.1, J11.1, Q4.1, R9.2, R13.1
NetD5_2: D5.2, R11.2
NetD6_1: D6.1, J12.1, Q3.1, R10.2, R14.1
NetD6_2: D6.2, R12.2
NetD8_2: D8.2, R29.2
NetD9_2: D9.2, R30.2
NetJ6_1: J6.1, U3.2, U5.6
NetJ7_1: J7.1, U2.2, U4.6
NetJ9_1: J9.1, U3.3, U5.4
NetJ10_1: J10.1, U2.3, U4.4
NetJ13_1: J13.1, Q3.3, Q4.3, R13.2, R14.2, R17.2, R22.2
NetQ5_G: Q5.G, R28.1, R31.2
NetR3_1: R3.1, R5.1, U3.7
NetR4_1: R4.1, R8.1, U2.7
NetR9_1: R9.1, R11.1, U3.5
NetR10_1: R10.1, R12.1, U2.5
NetR18_1: R18.1, U1.3
NetR20_2: R20.2, R23.2, U1.7
NetR23_1: R23.1, U1.6
NetR24_1: R24.1, U6.44
PB0: U4.3, U6.18
PB1: U4.1, U6.19
PB4: C34.2, R33.1, S2.2, U6.40
PB5: C35.2, R34.1, S3.2, U6.41
PB6: C36.2, R36.1, S4.2, U6.42
PB7: C37.2, R37.1, S5.2, U6.43
PB10: J8.1, U5.3, U6.21
PB11: J5.1, U5.1, U6.22
SDA: P4.1, U6.25
SWCLK: P3.2, U6.37
SWDIO: P3.4, U6.34
VDD3.3V: C7.1, C8.1, C21.2, C22.2, C23.2, C24.2, C25.2, C26.2, D8.1, D9.1, P3.1, P4.3, R27.2, R32.2, R33.2, R34.2, R36.2, R37.2, U4.5, U5.5, U6.1, U6.24, U6.36, U6.48, U7.2, U7.4
Vref 1.2V: R16.1, R35.1, U9.1
X1: C27.2, U6.5, Y1.2
X2: C28.2, U6.6, Y1.1

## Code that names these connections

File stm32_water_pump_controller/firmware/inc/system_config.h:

/**
 * @file system_config.h
 * @brief System Configuration & Parameters for STM32 Smart Water Pump Controller
 *
 * Defines pin mappings, ADC calibration constants, moisture thresholds,
 * and time-based safety limits.
 */

#ifndef SYSTEM_CONFIG_H
#define SYSTEM_CONFIG_H

#include <stdint.h>
#include <stdbool.h>

#ifdef __cplusplus
extern "C" {
#endif

/* ========================================================================= */
/* Hardware Pin Definitions (STM32F103C8T6 LQFP-48)                         */
/* ========================================================================= */

/* Soil Moisture Sensor Analog Front-End */
#define PIN_MOISTURE_ADC_PORT       GPIOA
#define PIN_MOISTURE_ADC_PIN        0           /* PA0: ADC1_IN0 */

/* Water Pump Power MOSFET Gate Control */
#define PIN_PUMP_GATE_PORT          GPIOB
#define PIN_PUMP_GATE_PIN           0           /* PB0: TIM3_CH3 or GPIO */

/* Diagnostic & Status LEDs */
#define PIN_LED_PUMP_PORT           GPIOB
#define PIN_LED_PUMP_PIN            12          /* PB12: Blue LED (Pump Active) */

#define PIN_LED_WARN_PORT           GPIOB
#define PIN_LED_WARN_PIN            13          /* PB13: Red LED (Low Moisture Alert) */

#define PIN_LED_STATUS_PORT         GPIOC
#define PIN_LED_STATUS_PIN          13          /* PC13: Green LED (System Heartbeat) */

/* User Input Pushbuttons */
#define PIN_BTN_OVERRIDE_PORT       GPIOA
#define PIN_BTN_OVERRIDE_PIN        8           /* PA8: Manual Pump Override (Active Low) */

/* ========================================================================= */
/* Soil Moisture Thresholds & Calibration                                   */
/* ========================================================================= */

/**
 * Capacitive / Resistive Soil Moisture Sensor Raw ADC Calibration:
 * Air (100% dry):     ~3400 counts (3.3V / 12-bit ADC)
 * Water (100% wet):   ~1200 counts (submerged in water)
 */
#define ADC_RAW_DRY_AIR             3400U
#define ADC_RAW_SATURATED_WATER     1200U

/* Moisture percentages (0 - 100%) */
#define MOISTURE_DRY_THRESHOLD_PCT  30U     /* Below 30%: Trigger irrigation cycle */
#define MOISTURE_TARGET_PCT         65U     /* Above 65%: Soil adequately hydrated, stop pump */
#define MOISTURE_ALERT_PCT          15U     /* Below 15%: Critical drought alert */

/* ========================================================================= */
/* Timing & Safety Limits (in Milliseconds)                                 */
/* ========================================================================= */

/* Maximum continuous pump run time before emergency safety shutoff */
#define PUMP_MAX_RUN_TIME_MS        (30U * 1000U)       /* 30 seconds max */

/* Soak / Cooldown delay to allow water absorption before next sensor check */
#define PUMP_COOLDOWN_TIME_MS       (300U * 1000U)      /* 5 minutes (300 seconds) */

/* Periodic moisture sensor sampling interval */
#define SENSOR_SAMPLE_INTERVAL_MS   (10U * 1000U)       /* 10 seconds */

/* Manual override test burst duration */
#define PUMP_MANUAL_BURST_MS        (5U * 1000U)        /* 5 seconds */

/* Button debounce threshold */
#define BUTTON_DEBOUNCE_MS          50U                 /* 50 ms */

/* Heartbeat LED blink period */
#define HEARTBEAT_NORMAL_PERIOD_MS  1000U               /* 1 Hz */
#define HEARTBEAT_ACTIVE_PERIOD_MS  200U                /* 5 Hz */

#ifdef __cplusplus
}
#endif

#endif /* SYSTEM_CONFIG_H */

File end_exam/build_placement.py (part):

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
        # --- CHANNEL A ---
        # Outputs along UPPER edge
        "J3": ("Connector_PinHeader_2.54mm", "PinHeader_1x02_P2.54mm_Vertical", 136.0, 107.0, 0, "SPK_A_8R", {"1": "SPK_A_POS", "2": "GND"}),
        # Inputs along LOWER edge
        "J2": ("Connector_PinHeader_2.54mm", "PinHeader_1x02_P2.54mm_Vertical", 136.0, 163.0, 0, "L_A_10mH", {"1": "+9V", "2": "TIMING_A"}),
        # NE555 Timer DIP-8
        "U1": ("Package_DIP", "DIP-8_W7.62mm", 138.0, 132.0, 0, "NE555P", {
            "1": "GND",
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        # Decoupling right at U1 Pin 8/1
        "C6": ("Capacitor_THT", "C_Disc_D4.3mm_W1.9mm_P5.00mm", 129.0, 117.0, 0, "100nF", {"1": "+9V", "2": "GND"}),
        "C7": ("Capacitor_THT", "CP_Radial_D5.0mm_P2.00mm", 139.0, 117.0, 0, "10uF", {"1": "+9V", "2": "GND"}),
        # Timing loop (compact near pins 7, 6, 2)
        "C3": ("Capacitor_THT", "CP_Radial_D5.0mm_P2.00mm", 127.0, 128.0, 0, "2.2uF", {"1": "TIMING_A", "2": "SENSE_A"}),
        "R2": ("Resistor_THT", "R_Axial_DIN0207_L6.3mm_D2.5mm_P7.62mm_Horizontal", 127.0, 140.0, 90, "47k", {"1": "SENSE_A", "2": "RC_A"}),
        "C4": ("Capacitor_THT", "CP_Radial_D5.0mm_P2.00mm", 127.0, 154.0, 0, "2.2uF", {"1": "RC_A", "2": "GND"}),
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
        # --- CHANNEL B ---
        # Outputs along UPPER edge
        "J5": ("Connector_PinHeader_2.54mm", "PinHeader_1x02_P2.54mm_Vertical", 168.0, 107.0, 0, "SPK_B_8R", {"1": "SPK_B_POS", "2": "GND"}),
        # Inputs along LOWER edge
        "J4": ("Connector_PinHeader_2.54mm", "PinHeader_1x02_P2.54mm_Vertical", 168.0, 163.0, 0, "L_B_10mH", {"1": "+9V", "2": "TIMING_B"}),
        # NE555 Timer DIP-8
        "U2": ("Package_DIP", "DIP-8_W7.62mm", 168.0, 132.0, 0, "NE555P", {
            "1": "GND",
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        # Decoupling right at U2 Pin 8/1
        "C11": ("Capacitor_THT", "C_Disc_D4.3mm_W1.9mm_P5.00mm", 159.0, 117.0, 0, "100nF", {"1": "+9V", "2": "GND"}),
        "C12": ("Capacitor_THT", "CP_Radial_D5.0mm_P2.00mm", 169.0, 117.0, 0, "10uF", {"1": "+9V", "2": "GND"}),
        # Timing loop (compact near pins 7, 6, 2)
        "C8": ("Capacitor_THT", "CP_Radial_D5.0mm_P2.00mm", 157.0, 128.0, 0, "2.2uF", {"1": "TIMING_B", "2": "SENSE_B"}),
        "R3": ("Resistor_THT", "R_Axial_DIN0207_L6.3mm_D2.5mm_P7.62mm_Horizontal", 157.0, 140.0, 90, "47k", {"1": "SENSE_B", "2": "RC_B"}),
        "C9": ("Capacitor_THT", "CP_Radial_D5.0mm_P2.00mm", 157.0, 154.0, 0, "2.2uF", {"1": "RC_B", "2": "GND"}),
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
